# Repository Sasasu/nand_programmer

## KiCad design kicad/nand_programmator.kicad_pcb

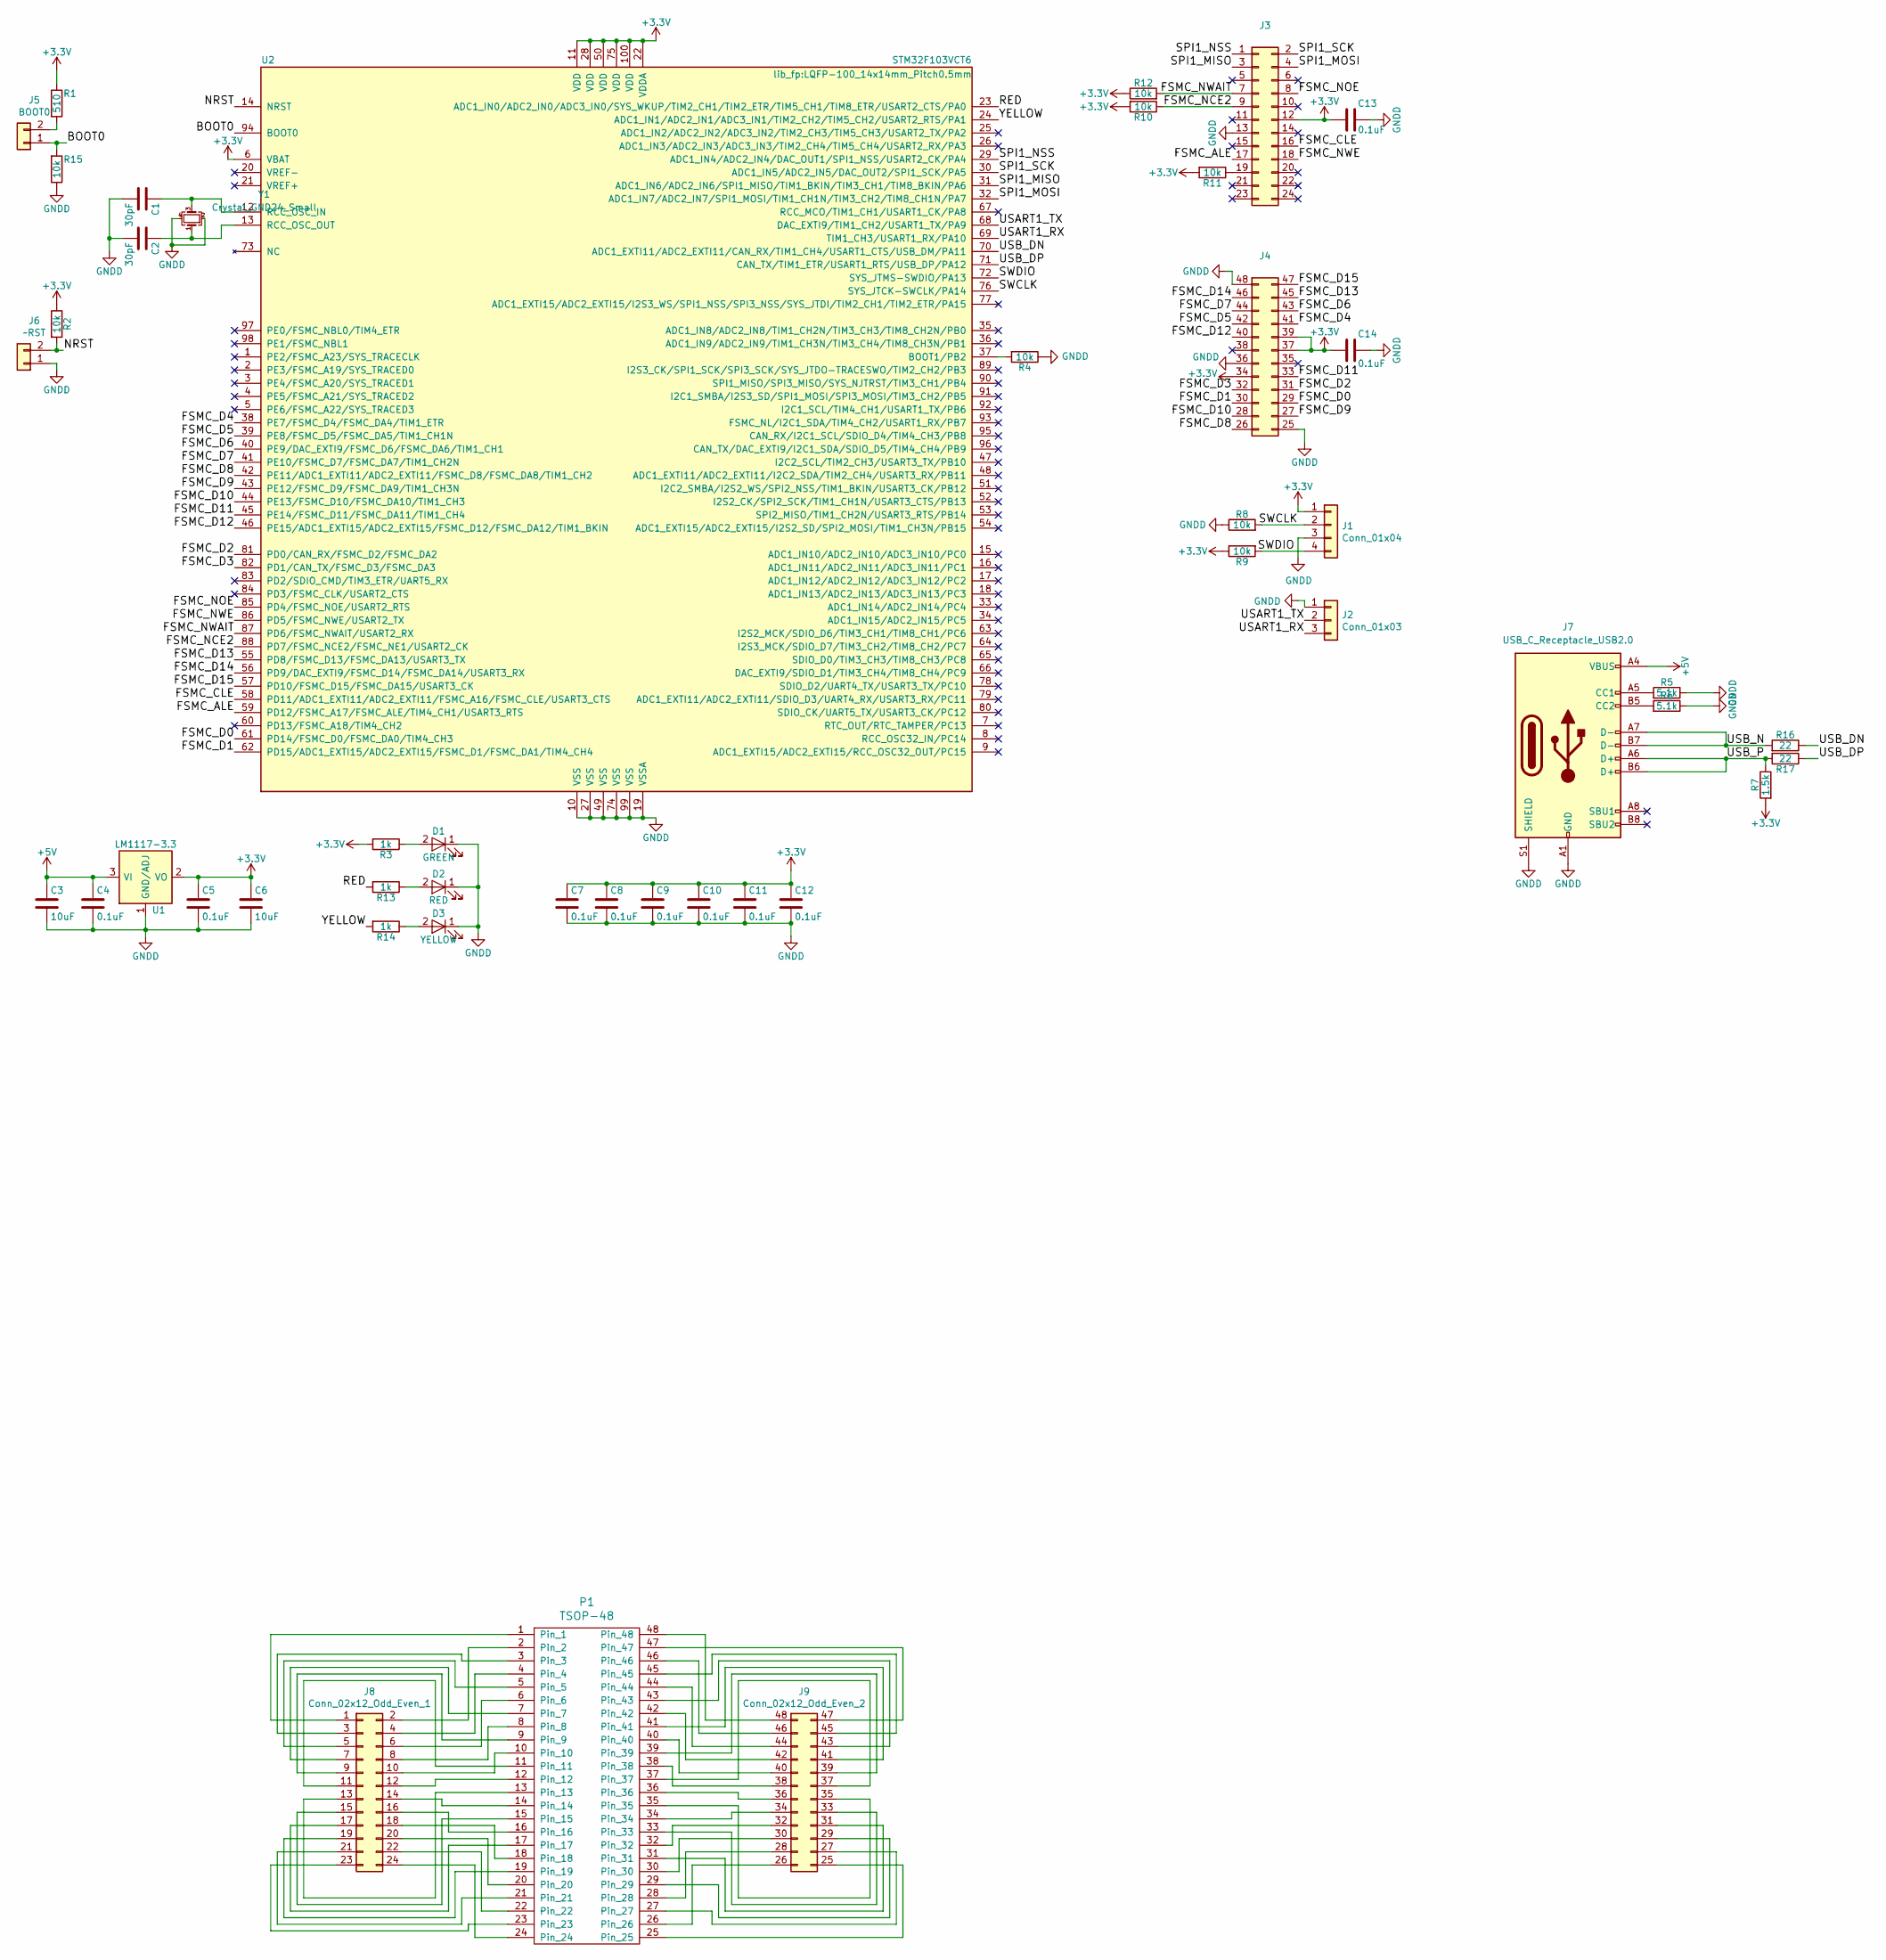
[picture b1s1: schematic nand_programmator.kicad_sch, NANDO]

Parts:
C1, C2: 30pF; C_0402_1005Metric; Farnell Ref 2905258
C3, C6: 10uF; C_0603_1608Metric; Farnell Ref 2112850
C4, C5, C7, C8, C9, C10, C11, C12, C13, C14: 0.1uF; C_0402_1005Metric; Farnell Ref 2320839
D1: GREEN; LED_0402_1005Metric; Farnell Ref 2099239
D2: RED; LED_0402_1005Metric; Farnell Ref 2099236
D3: YELLOW; LED_0402_1005Metric; Farnell Ref 2099243
J1: Conn_01x04; PinHeader_1x04_P2.54mm_Vertical; Farnell Ref 3049529
J2: Conn_01x03; PinHeader_1x03_P2.54mm_Vertical; Farnell Ref 3049527
J3: Conn_02x12_Odd_Even_Left; PinHeader_2x12_P2.54mm_Vertical; Farnell Ref 3049468
J4: Conn_02x12_Odd_Even_Right; PinHeader_2x12_P2.54mm_Vertical_2; Farnell Ref 3049468
J5: BOOT0; SolderJumper-2_P1.3mm_Open_RoundedPad1.0x1.5mm
J6: ~RST; SolderJumper-2_P1.3mm_Open_RoundedPad1.0x1.5mm
J7: USB_C_Receptacle_USB2.0; USB_C_Receptacle_HRO_TYPE-C-31-M-12
J8: Conn_02x12_Odd_Even_1; PinSocket_2x12_P2.54mm_Vertical
J9: Conn_02x12_Odd_Even_2; PinSocket_2x12_P2.54mm_Vertical_2
P1: TSOP-48; TSOP-I-48_18.4x12mm_P0.5mm
R1: 510; R_0402_1005Metric; Farnell Ref 2447679
R2, R4, R8, R9, R10, R11, R12, R15: 10k; R_0402_1005Metric; Farnell Ref 2447553
R3, R13, R14: 1k; R_0402_1005Metric; Farnell Ref 2447587
R5, R6: 5.1k; R_0402_1005Metric; Farnell Ref 2447592
R7: 1.5k; R_0402_1005Metric; Farnell Ref 2447592
R16, R17: 22; R_0402_1005Metric; Farnell Ref 2447609
U1: LM1117-3.3; SOT-223; Farnell Ref 3007498
U2: STM32F103VCT6; LQFP-100_14x14mm_Pitch0.5mm; Farnell Ref 1624139
Y1: Crystal_GND24_Small; Crystal_SMD_3225-4Pin_3.2x2.5mm

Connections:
+3V3: C5.1, C6.1, C7.1, C8.1, C9.1, C10.1, C11.1, C12.1, C13.2, C14.2, J1.1, J3.12, J4.34, J4.37, J4.39, R1.1, R2.1, R3.2, R7.2, R9.1, R10.2, R11.2, R12.1, U1.2 (VO), U1.4 (VO), U2.6 (VBAT), U2.11 (VDD), U2.22 (VDDA), U2.28 (VDD), U2.50 (VDD), U2.75 (VDD), U2.100 (VDD)
+5V: C3.1, C4.1, J7.A4 (VBUS), J7.A9 (VBUS), J7.B4 (VBUS), J7.B9 (VBUS), U1.3 (VI)
/BOOT0: J5.1, R15.2, U2.94 (BOOT0)
/FSMC_ALE: J3.17, U2.59 (PD12/FSMC_A17/FSMC_ALE/TIM4_CH1/USART3_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)
/FSMC_CLE: J3.16, U2.58 (PD11/ADC1_EXTI11/ADC2_EXTI11/FSMC_A16/F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)
/FSMC_D0: J4.29, U2.61 (PD14/FSMC_D0/FSMC_DA0/TIM4_CH3)
/FSMC_D1: J4.30, U2.62 (PD15/ADC1_EXTI15/ADC2_EXTI15/FSMC_D1/FS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)
/FSMC_D2: J4.31, U2.81 (PD0/CAN_RX/FSMC_D2/FSMC_DA2)
/FSMC_D3: J4.32, U2.82 (PD1/CAN_TX/FSMC_D3/FSMC_DA3)
/FSMC_D4: J4.41, U2.38 (PE7/FSMC_D4/FSMC_DA4/TIM1_ETR)
/FSMC_D5: J4.42, U2.39 (PE8/FSMC_D5/FSMC_DA5/TIM1_CH1N)
/FSMC_D6: J4.43, U2.40 (PE9/DAC_EXTI9/FSMC_D6/FSMC_DA6/TIM1_CH1)
/FSMC_D7: J4.44, U2.41 (PE10/FSMC_D7/FSMC_DA7/TIM1_CH2N)
/FSMC_D8: J4.26, U2.42 (PE11/ADC1_EXTI11/ADC2_EXTI11/FSMC_D8/FS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)
/FSMC_D9: J4.27, U2.43 (PE12/FSMC_D9/FSMC_DA9/TIM1_CH3N)
/FSMC_D10: J4.28, U2.44 (PE13/FSMC_D10/FSMC_DA10/TIM1_CH3)
/FSMC_D11: J4.33, U2.45 (PE14/FSMC_D11/FSMC_DA11/TIM1_CH4)
/FSMC_D12: J4.40, U2.46 (PE15/ADC1_EXTI15/ADC2_EXTI15/FSMC_D12/F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)
/FSMC_D13: J4.45, U2.55 (PD8/FSMC_D13/FSMC_DA13/USART3_TX)
/FSMC_D14: J4.46, U2.56 (PD9/DAC_EXTI9/FSMC_D14/FSMC_DA14/USART3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)
/FSMC_D15: J4.47, U2.57 (PD10/FSMC_D15/FSMC_DA15/USART3_CK)
/FSMC_NCE2: J3.9, R10.1, U2.88 (PD7/FSMC_NCE2/FSMC_NE1/USART2_CK)
/FSMC_NOE: J3.8, U2.85 (PD4/FSMC_NOE/USART2_RTS)
/FSMC_NWAIT: J3.7, R12.2, U2.87 (PD6/FSMC_NWAIT/USART2_RX)
/FSMC_NWE: J3.18, U2.86 (PD5/FSMC_NWE/USART2_TX)
/NRST: J6.2, R2.2, U2.14 (NRST)
/RED: R13.2, U2.23 (ADC1_IN0/ADC2_IN0/ADC3_IN0/SYS_WKUP/TIM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)
/SPI1_MISO: J3.3, U2.31 (ADC1_IN6/ADC2_IN6/SPI1_MISO/TIM1_BKIN/T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)
/SPI1_MOSI: J3.4, U2.32 (ADC1_IN7/ADC2_IN7/SPI1_MOSI/TIM1_CH1N/T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)
/SPI1_NSS: J3.1, U2.29 (ADC1_IN4/ADC2_IN4/DAC_OUT1/SPI1_NSS/USA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)
/SPI1_SCK: J3.2, U2.30 (ADC1_IN5/ADC2_IN5/DAC_OUT2/SPI1_SCK/PA5)
/SWCLK: J1.2, R8.2, U2.76 (SYS_JTCK-SWCLK/PA14)
/SWDIO: J1.4, R9.2, U2.72 (SYS_JTMS-SWDIO/PA13)
/USART1_RX: J2.3, U2.69 (TIM1_CH3/USART1_RX/PA10)
/USART1_TX: J2.2, U2.68 (DAC_EXTI9/TIM1_CH2/USART1_TX/PA9)
/USB_DN: R16.1, U2.70 (ADC1_EXTI11/ADC2_EXTI11/CAN_RX/TIM1_CH4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)
/USB_DP: R17.1, U2.71 (CAN_TX/TIM1_ETR/USART1_RTS/USB_DP/PA12)
/USB_N: J7.A7 (D-), J7.B7 (D-), R16.2
/USB_P: J7.A6 (D+), J7.B6 (D+), R7.1, R17.2
/YELLOW: R14.2, U2.24 (ADC1_IN1/ADC2_IN1/ADC3_IN1/TIM2_CH2/TIM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)
GNDD: C1.2, C2.2, C3.2, C4.2, C5.2, C6.2, C7.2, C8.2, C9.2, C10.2, C11.2, C12.2, C13.1, C14.1, D1.1 (K), D2.1 (K), D3.1 (K), J1.3, J2.1, J3.13, J4.25, J4.36, J4.48, J6.1, J7.A1 (GND), J7.A12 (GND), J7.B1 (GND), J7.B12 (GND), J7.S1 (SHIELD), R4.1, R5.1, R6.1, R8.1, R15.1, U1.1 (GND/ADJ), U2.10 (VSS), U2.19 (VSSA), U2.27 (VSS), U2.49 (VSS), U2.74 (VSS), U2.99 (VSS), Y1.2, Y1.4
unnamed: C1.1, U2.12 (RCC_OSC_IN), Y1.3
unnamed: C2.1, U2.13 (RCC_OSC_OUT), Y1.1
unnamed: D1.2 (A), R3.1
unnamed: D2.2 (A), R13.1
unnamed: D3.2 (A), R14.1
unnamed: J3.19, R11.1
unnamed: J5.2, R1.2
unnamed: J7.A5 (CC1), R5.2
unnamed: J7.B5 (CC2), R6.2
unnamed: J8.1, P1.1
unnamed: J8.2, P1.2
unnamed: J8.3, P1.3
unnamed: J8.4, P1.4
unnamed: J8.5, P1.5
unnamed: J8.6, P1.6
unnamed: J8.7, P1.7
unnamed: J8.8, P1.8
unnamed: J8.9, P1.9
unnamed: J8.10, P1.10
unnamed: J8.11, P1.11
unnamed: J8.12, P1.12
unnamed: J8.13, P1.13
unnamed: J8.14, P1.14
unnamed: J8.15, P1.15
unnamed: J8.16, P1.16
unnamed: J8.17, P1.17
unnamed: J8.18, P1.18
unnamed: J8.19, P1.19
unnamed: J8.20, P1.20
unnamed: J8.21, P1.21
unnamed: J8.22, P1.22
unnamed: J8.23, P1.23
unnamed: J8.24, P1.24
unnamed: J9.25, P1.25
unnamed: J9.26, P1.26
unnamed: J9.27, P1.27
unnamed: J9.28, P1.28
unnamed: J9.29, P1.29
unnamed: J9.30, P1.30
unnamed: J9.31, P1.31
unnamed: J9.32, P1.32
unnamed: J9.33, P1.33
unnamed: J9.34, P1.34
unnamed: J9.35, P1.35
unnamed: J9.36, P1.36
unnamed: J9.37, P1.37
unnamed: J9.38, P1.38
unnamed: J9.39, P1.39
unnamed: J9.40, P1.40
unnamed: J9.41, P1.41
unnamed: J9.42, P1.42
unnamed: J9.43, P1.43
unnamed: J9.44, P1.44
unnamed: J9.45, P1.45
unnamed: J9.46, P1.46
unnamed: J9.47, P1.47
unnamed: J9.48, P1.48
unnamed: R4.2, U2.37 (BOOT1/PB2)

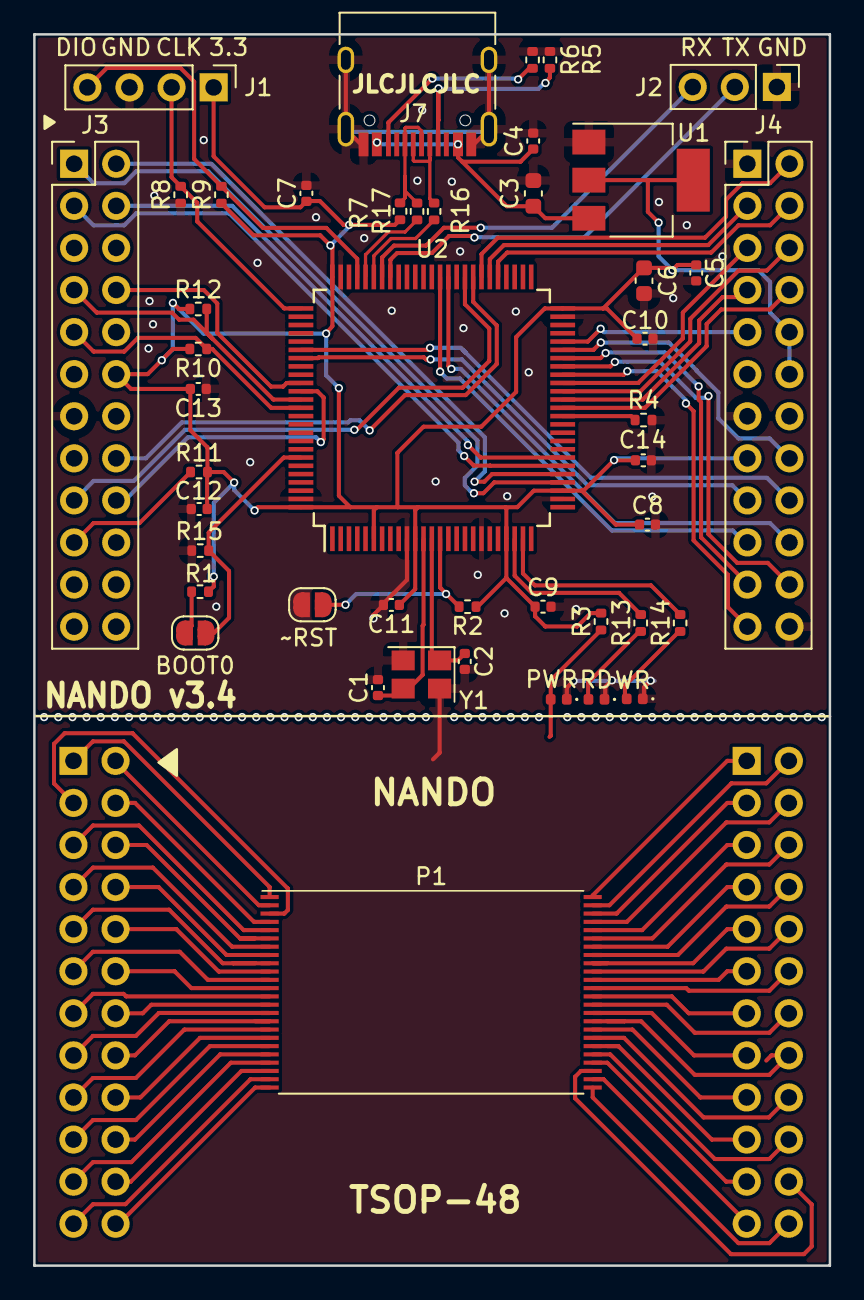
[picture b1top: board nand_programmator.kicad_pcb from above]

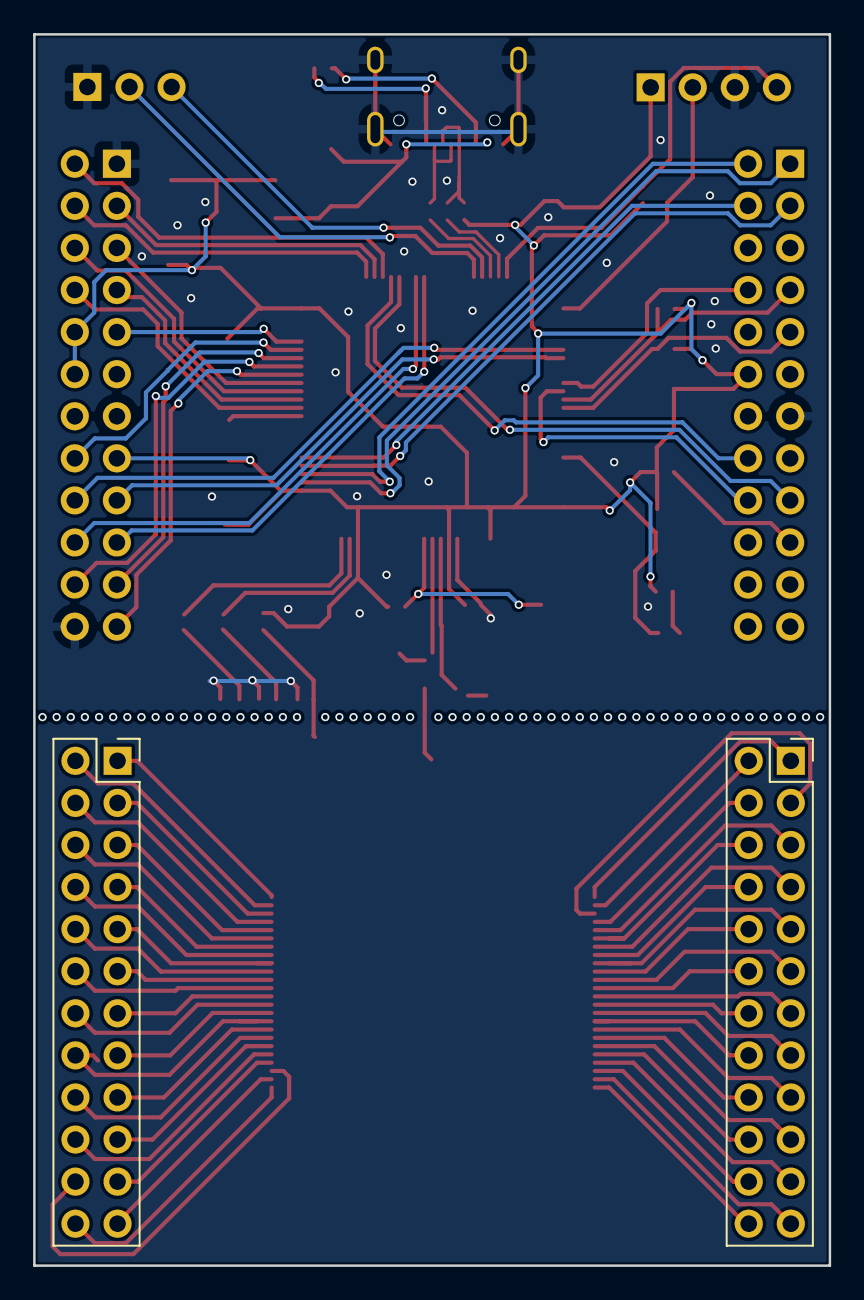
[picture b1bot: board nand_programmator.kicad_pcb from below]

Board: 2 copper layers, 48.0 x 74.3 mm, 47 parts (2 on the bottom side), 99 nets.

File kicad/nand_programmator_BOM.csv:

"Comment","Description","Designator","Footprint","LibRef","Pins","Quantity","PartNumber","url",
"30pF","desc","C1,C2,","C_0402_1005Metric","libref","2","2","","",
"10uF","desc","C3,C6,","C_0603_1608Metric","libref","2","2","","",
"0.1uF","desc","C4,C5,C7,C8,C9,C10,C11,C12,C13,C14,","C_0402_1005Metric","libref","2","10","","",
"GREEN","desc","D1,","LED_0402_1005Metric","libref","2","1","","",
"RED","desc","D2,","LED_0402_1005Metric","libref","2","1","","",
"YELLOW","desc","D3,","LED_0402_1005Metric","libref","2","1","","",
"BOOT0","desc","J5,","SolderJumper-2_P1.3mm_Open_RoundedPad1.0x1.5mm","libref","2","1","","",
"~RST","desc","J6,","SolderJumper-2_P1.3mm_Open_RoundedPad1.0x1.5mm","libref","2","1","","",
"TSOP-48","desc","P1,","TSOP-I-48_18.4x12mm_P0.5mm","libref","48","1","","",
"510","desc","R1,","R_0402_1005Metric","libref","2","1","","",
"10k","desc","R2,R4,R8,R9,R10,R11,R12,R15,","R_0402_1005Metric","libref","2","8","","",
"1k","desc","R3,R13,R14,","R_0402_1005Metric","libref","2","3","","",
"5.1k","desc","R5,R6,","R_0402_1005Metric","libref","2","2","","",
"1.5k","desc","R7,","R_0402_1005Metric","libref","2","1","","",
"22","desc","R16,R17,","R_0402_1005Metric","libref","2","2","","",
"LM1117-3.3","desc","U1,","SOT-223","libref","4","1","","",
"STM32F103VCT6","desc","U2,","LQFP-100_14x14mm_Pitch0.5mm","libref","100","1","","",
"Crystal_GND24_Small","desc","Y1,","Crystal_SMD_3225-4Pin_3.2x2.5mm","libref","4","1","","",
"Through Hole Items ",
"Conn_01x04","desc","J1,","PinHeader_1x04_P2.54mm_Vertical","libref","4","1","","~",
"Conn_01x03","desc","J2,","PinHeader_1x03_P2.54mm_Vertical","libref","3","1","","~",
"Conn_02x12_Odd_Even_Left","desc","J3,","PinHeader_2x12_P2.54mm_Vertical","libref","24","1","","~",
"Conn_02x12_Odd_Even_Right","desc","J4,","PinHeader_2x12_P2.54mm_Vertical_2","libref","24","1","","~",
"USB_C_Receptacle_USB2.0","desc","J7,","USB_C_Receptacle_HRO_TYPE-C-31-M-12","libref","22","1","","",
"Conn_02x12_Odd_Even_1","desc","J8,","PinSocket_2x12_P2.54mm_Vertical","libref","24","1","","",
"Conn_02x12_Odd_Even_2","desc","J9,","PinSocket_2x12_P2.54mm_Vertical_2","libref","24","1","","",

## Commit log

2023-02-22 smd 0405
2023-03-01 Qt: fix compile error when ODR check enabled.
    when two structs with the same name, the linker many be confused. when LTO
    is enabled, ODR checked is required.
    ```
    parallel_chip_info.cpp:36:3: error: type ‘struct Conf’ violates the C++ One Definition Rule [-Werror=odr]
    36 | } Conf;
    | ^
